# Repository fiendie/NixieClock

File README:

This Arduino Sketch controls a NIXIE clock with 4 tubes. 
I used a plain ATMega168 microcontroller instead of an Arduino board for obvious reasons.
Here is a picture of the circuit board: https://github.com/fiendie/NixieClock/raw/master/images/circuit.jpg

I am using a DS1307 RTC chip to keep track of the time. 

The schematics can be found here: https://github.com/fiendie/NixieClock/tree/master/schematics

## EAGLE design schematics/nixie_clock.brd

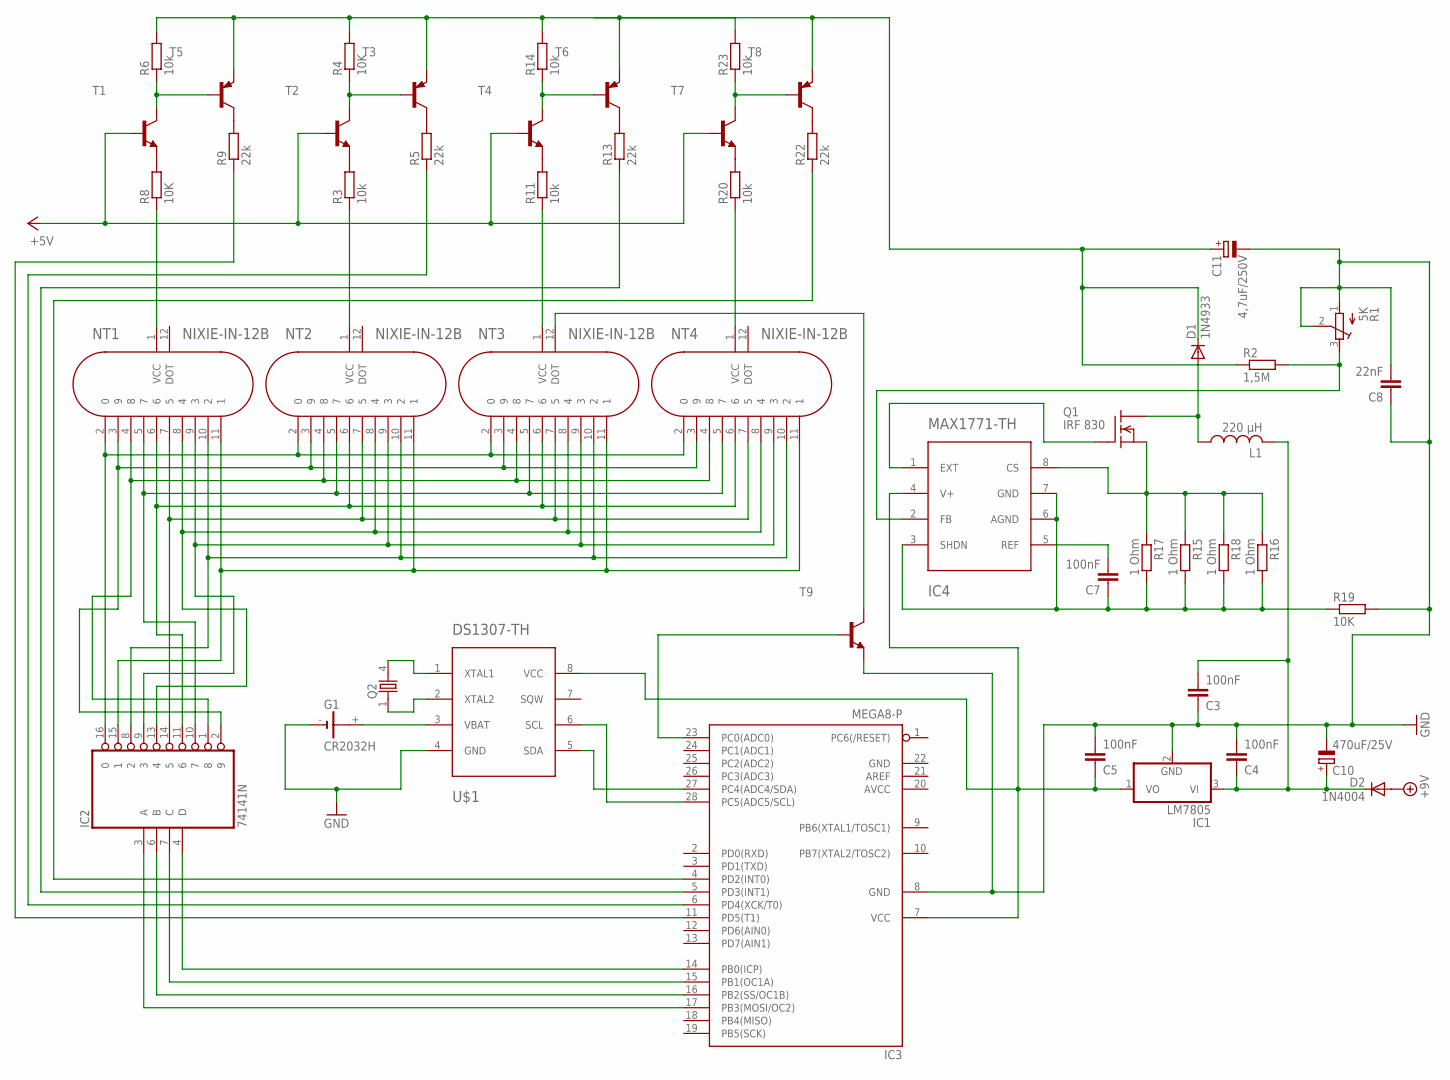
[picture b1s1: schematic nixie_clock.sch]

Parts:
C3, C4, C5, C7: 100nF; C5B2.5
C8: 22nF; C5B2.5
C10: 470uF/25V; E2,5-6E
C11: 4,7uF/250V; E2,5-6E
D1: 1N4933; DO41-10
D2: 1N4004; DO41-10
G1: CR2032H
IC1: LM7805; TO92
IC2: 74141N; DIL16
IC3: MEGA8-P; DIL28-3
IC4: MAX1771-TH; MAX1771
L1: 220 µH; TJ4-U2
NT1, NT2, NT3, NT4: NIXIE-IN-12B; NIXIE
Q1: IRF 830; TO220
Q2: 86SMX
R1: 5K; RTRIM4G/J
R2: 1,5M; 0207/10
R3, R6, R11, R14, R20, R23: 10k; 0207/10
R4, R8, R19: 10K; 0207/10
R5, R9, R13, R22: 22k; 0207/10
R15, R16, R17, R18: 1 Ohm; 0207/10
T1, T2, T4, T7, T9: MPSA44-NPN-TO92-CBE; TO92-CBE
T3, T5, T6, T8: MPSA64-PNP-TO92-CBE; TO92-CBE
U$1: DS1307-TH; DS1307

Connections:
+5V: T1.B, T2.B, T4.B, T7.B
+9V: D2.A
AVCC: IC3.20 (AVCC)
GND: C3.1, C4.2, C5.2, C8.1, C8.2, C10.-, C11.-, G1.-, IC1.2 (GND), IC2.12 (GND), IC3.8 (GND), IC3.22 (GND), R1.1 (E), R1.2 (S), R19.2, T9.E, U$1.4 (GND)
IC5: Q2.1, U$1.2 (XTAL2)
MAX1771: IC4.1 (EXT), Q1.1 (G)
unnamed: R6.1, T1.C, T5.B
unnamed: R4.1, T2.C, T3.B
unnamed: R9.2, T5.C
unnamed: IC4.2 (FB), R1.3 (A), R2.2
unnamed: R14.1, T4.C, T6.B
unnamed: R5.2, T3.C
unnamed: R23.1, T7.C, T8.B
unnamed: R13.2, T6.C
unnamed: R22.2, T8.C
unnamed: R8.2, T1.E
unnamed: R3.2, T2.E
unnamed: R11.2, T4.E
unnamed: R20.2, T7.E
unnamed: IC2.16 (0), NT1.2 (0), NT2.2 (0), NT3.2 (0), NT4.2 (0)
unnamed: C11.+, D1.C, R2.1, T8.E
unnamed: IC2.8 (2), NT1.10 (2), NT2.10 (2), NT3.10 (2), NT4.10 (2)
unnamed: IC2.9 (3), NT1.9 (3), NT2.9 (3), NT3.9 (3), NT4.9 (3)
unnamed: IC2.13 (4), NT1.8 (4), NT2.8 (4), NT3.8 (4), NT4.8 (4)
unnamed: NT2.1 (VCC), R3.1
unnamed: NT3.1 (VCC), R11.1
unnamed: NT4.1 (VCC), R20.1
unnamed: IC3.11 (PD5(T1)), R9.1
unnamed: D1.A, L1.1, Q1.2 (D)
unnamed: C5.1, IC1.1 (VO), IC3.7 (VCC), IC4.4 (V+), U$1.8 (VCC)
unnamed: IC4.8 (CS), Q1.3 (S), R15.1, R16.1, R17.1, R18.1
unnamed: IC3.6 (PD4(XCK/T0)), R5.1
unnamed: IC3.5 (PD3(INT1)), R13.1
unnamed: C7.2, IC4.5 (REF)
unnamed: C3.2, C4.1, C10.+, D2.C, IC1.3 (VI), L1.2
unnamed: IC3.4 (PD2(INT0)), R22.1
unnamed: IC2.14 (5), NT1.7 (5), NT2.7 (5), NT3.7 (5), NT4.7 (5)
unnamed: IC2.11 (6), NT1.6, NT2.6, NT3.6, NT4.6
unnamed: IC2.10 (7), NT1.5 (7), NT2.5 (7), NT3.5 (7), NT4.5 (7)
unnamed: IC2.1 (8), NT1.4 (8), NT2.4 (8), NT3.4 (8), NT4.4 (8)
unnamed: IC2.2 (9), NT1.3 (9), NT2.3 (9), NT3.3 (9), NT4.3 (9)
unnamed: IC2.4 (D), IC3.14 (PB0(ICP))
unnamed: IC2.7 (C), IC3.15 (PB1(OC1A))
unnamed: IC2.6 (B), IC3.16 (PB2(SS/OC1B))
unnamed: IC2.3 (A), IC3.17 (PB3(MOSI/OC2))
unnamed: IC3.27 (PC4(ADC4/SDA)), U$1.5 (SDA)
unnamed: IC3.28 (PC5(ADC5/SCL)), U$1.6 (SCL)
unnamed: IC2.15 (1), NT1.11 (1), NT2.11 (1), NT3.11 (1), NT4.11 (1)
unnamed: R4.2, R6.2, R14.2, R23.2, T3.E, T5.E, T6.E
unnamed: Q2.4 (2), U$1.1 (XTAL1)
unnamed: C7.1, IC4.3 (SHDN), IC4.6 (AGND), IC4.7 (GND), R15.2, R16.2, R17.2, R18.2, R19.1
unnamed: G1.+, U$1.3 (VBAT)
unnamed: NT3.12 (DOT), T9.C
unnamed: IC3.23 (PC0(ADC0)), T9.B
NT1: NT1.1 (VCC), R8.1
VCC: IC2.5 (VCC)

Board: 2 copper layers, 50 parts (0 on the bottom side), 53 nets, no tracks yet.

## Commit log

2012-02-05 Removed the PCF8583 dependency, added animation
    I exchanged the PCF8583 chip with a DS1307 because it has a dedicated
    battery input pin and because the PCF8583 seemed to be inaccurate. But
    that turned out to be a problem with the interference from the NIXIE
    power supply (which I still haven't resolved).
2012-02-05 Removed reference to the PCF8583 library
2012-02-08 Some fixes
2012-02-11 Added a watchdog timer for extra reliability
2012-02-18 Added Schematics
2012-02-19 Added Images
2012-02-28 Updated Schematics
2012-03-02 Arduino 1.0 compatibility
2012-03-05 Arduino 1.0 Compatibility Fixes
2020-10-22 Use PlatformIO instead of Makefile, refactored to use RTCLib and Bounce2 libraries
